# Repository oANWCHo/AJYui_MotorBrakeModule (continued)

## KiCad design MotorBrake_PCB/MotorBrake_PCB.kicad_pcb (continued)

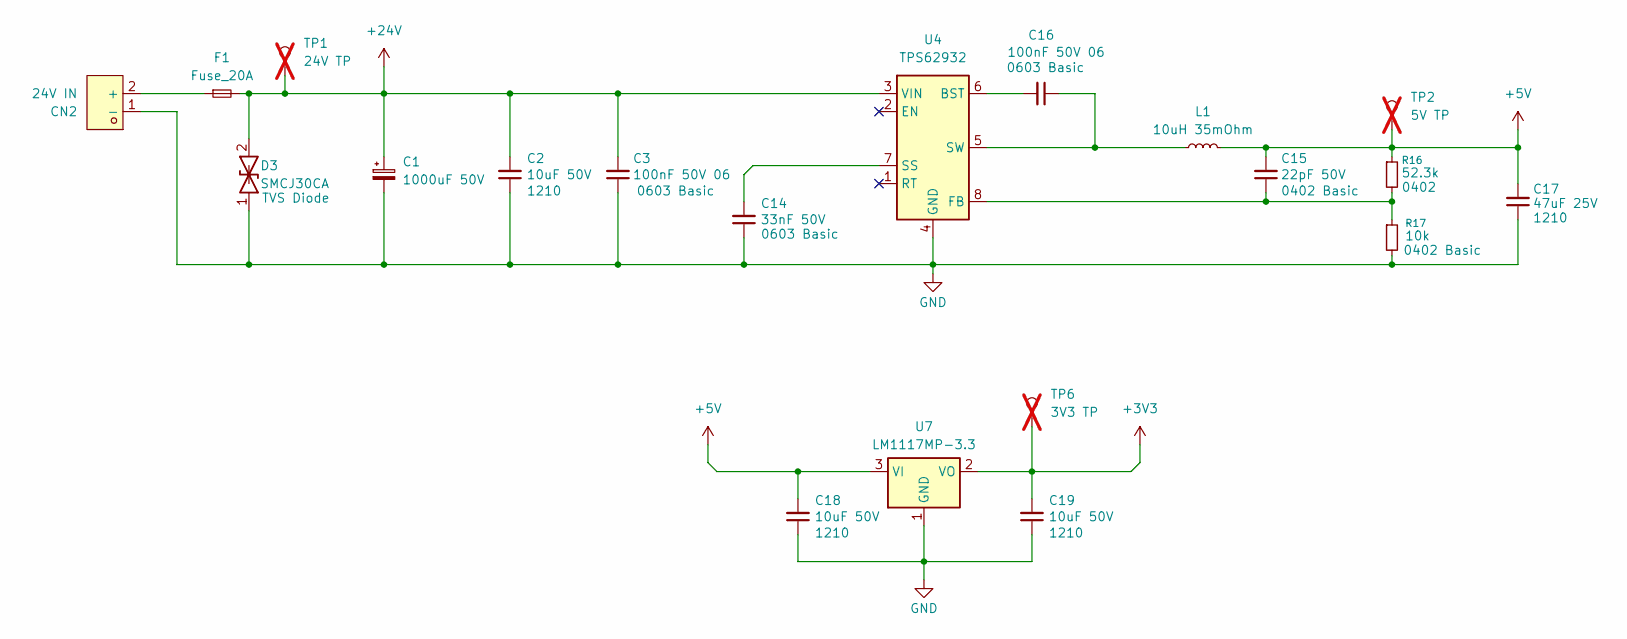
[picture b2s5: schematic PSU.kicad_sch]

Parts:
C1: 1000uF 50V; CP_Elec_16x17.5; JLCPCB Part # C5266058
C2, C18, C19: 10uF 50V; C_1210_3225Metric; JLCPCB Part # C2918502
C3, C16: 100nF 50V 06; C_0603_1608Metric; JLCPCB Part # C14663
C14: 33nF 50V; C_0603_1608Metric; JLCPCB Part # C21117
C15: 22pF 50V; C_0402_1005Metric; JLCPCB Part # C1555
C17: 47uF 25V; C_1210_3225Metric; JLCPCB Part # C6120020
CN2: 24V IN; CONN-TH_XT30UPB-M; Manufacturer Part XT30UPB-M; LCSC Part Name AMASS(艾迈斯)板载立式 航模锂电池控制器连接器插头 PCB板立式 公头X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
D3: SMCJ30CA; SMC_L6.9-W5.9-LS7.9-BI; JLCPCB Part # C7470406
F1: Fuse_20A; CONN-TH_XF-507P; JLCPCB Part # C668119
L1: 10uH 35mOhm; L_TechFuse_SL1040; JLCPCB Part # C22463843
R16: 52.3k; R_0402_1005Metric; JLCPCB Part # C26982
R17: 10k; R_0402_1005Metric; JLCPCB Part # C25744
TP1: 24V TP; TestPoint_Pad_1.0x1.0mm; not fitted
TP2: 5V TP; TestPoint_Pad_1.0x1.0mm; not fitted
TP6: 3V3 TP; TestPoint_Pad_1.0x1.0mm; not fitted
U4: TPS62932; SOT-583-8; JLCPCB Part # C3032935
U7: LM1117MP-3.3; SOT-223-3_TabPin2; JLCPCB Part # C6186

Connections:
+3V3: C19.2, TP6.1 (1_1), U7.2 (VO); also elsewhere on the board
+5V: C15.2, C17.2, C18.2, L1.2, R16.1, TP2.1 (1_1), U7.3 (VI); also elsewhere on the board
+24V: C1.1, C2.2, C3.2, D3.2, F1.2, TP1.1 (1_1), U4.3 (VIN); also elsewhere on the board
GND: C1.2, C2.1, C3.1, C14.1, C17.1, C18.1, C19.1, CN2.1 (-), D3.1, R17.2, U4.4 (GND), U7.1 (GND); also elsewhere on the board
unnamed: CN2.2 (+), F1.1
unnamed: C16.2, U4.6 (BST)
unnamed: C15.1, R16.2, R17.1, U4.8 (FB)
unnamed: C14.2, U4.7 (SS)
unnamed: C16.1, L1.1, U4.5 (SW)

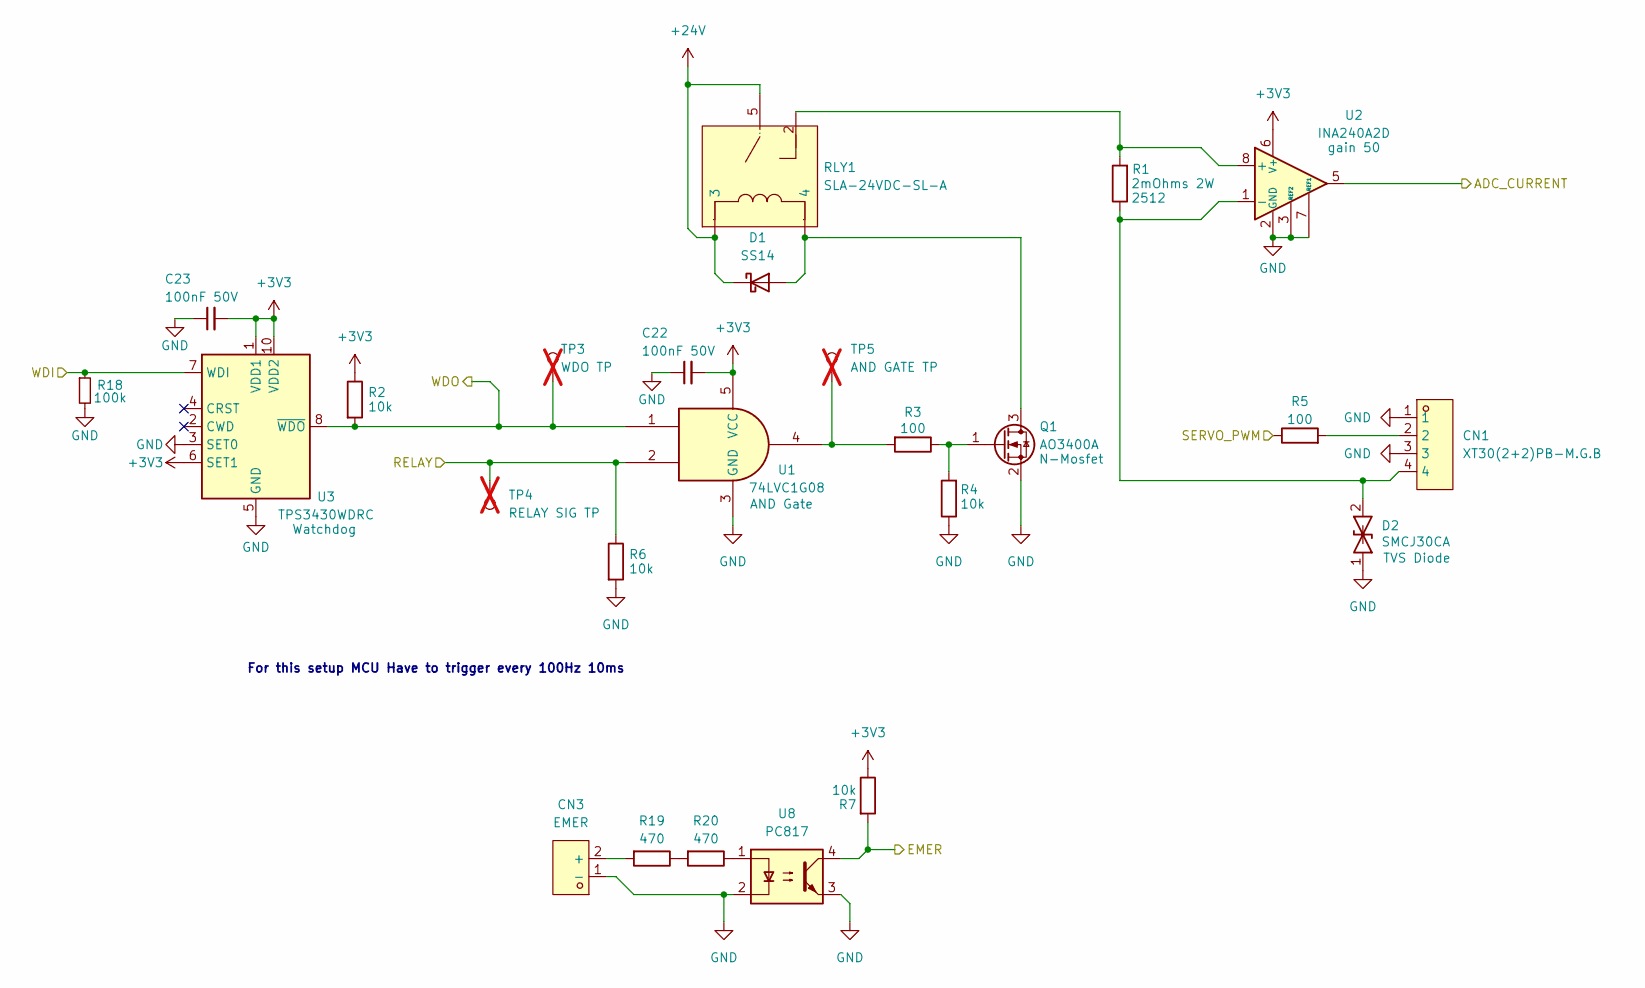
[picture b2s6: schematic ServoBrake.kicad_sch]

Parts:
C22, C23: 100nF 50V; C_0402_1005Metric; LCSC Part # C1525
CN1: XT30(2+2)PB-M.G.B; CONN-TH_XT30PB-M; Manufacturer Part XT30(2+2)PB-M.G.B; LCSC Part Name AMASS(艾迈斯)功率数据混合插头 PCB直插 板立式 金黑 公头XT30(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
CN3: EMER; CONN-TH_XT30UPB-M; Manufacturer Part XT30UPB-M; LCSC Part Name AMASS(艾迈斯)板载立式 航模锂电池控制器连接器插头 PCB板立式 公头X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
D1: SS14; D_SMA; JLCPCB Part # C2480
D2: SMCJ30CA; SMC_L6.9-W5.9-LS7.9-BI; JLCPCB Part # C7470406
Q1: AO3400A; SOT-23; JLCPCB Part # C20917
R1: 2mOhms 2W; R_2512_6332Metric; JLCPCB Part # C844691
R2, R4, R6, R7: 10k; R_0402_1005Metric; JLCPCB Part # C25744
R3, R5: 100; R_0603_1608Metric; JLCPCB Part # C22775
R18: 100k; R_0402_1005Metric; LCSC Part # C25741
R19, R20: 470; R_0603_1608Metric; JLCPCB Part # C23179
RLY1: SLA-24VDC-SL-A; RELAY-TH_SLA-XXVDC-SL-A; Manufacturer Part SLA-24VDC-SL-A; LCSC Part Name 小型大功率继电器(5P)
TP3: WDO TP; TestPoint_Pad_1.0x1.0mm; not fitted
TP4: RELAY SIG TP; TestPoint_Pad_1.0x1.0mm; not fitted
TP5: AND GATE TP; TestPoint_Pad_1.0x1.0mm; not fitted
U1: 74LVC1G08; SOT-23-5; JLCPCB Part # C19829660
U2: INA240A2D; SOIC-8_3.9x4.9mm_P1.27mm; JLCPCB Part # C2060768
U3: TPS3430WDRC; VSON-10-1EP_3x3mm_P0.5mm_EP1.65x2.4mm; JLCPCB Part # C2870545
U8: PC817; DIP-4_W7.62mm; JLCPCB Part # C5350

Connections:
+3V3: C22.2, C23.2, R2.1, R7.1, U1.5 (VCC), U2.6 (V+), U3.1 (VDD1), U3.6 (SET1), U3.10 (VDD2); also elsewhere on the board
+24V: D1.1 (K), RLY1.3, RLY1.5; also elsewhere on the board
/MCU/ADC_CURRENT: U2.5; also elsewhere on the board
/MCU/PC13: R7.2, U8.4; also elsewhere on the board
/MCU/RELAY: R6.1, TP4.1 (1_1), U1.2; also elsewhere on the board
/MCU/SERVO_PWM: R5.1; also elsewhere on the board
/MCU/WDI: R18.1, U3.7 (WDI); also elsewhere on the board
/MCU/WDO: R2.2, TP3.1 (1_1), U1.1, U3.8 (~WDO); also elsewhere on the board
GND: C22.1, C23.1, CN1.1, CN1.3, CN3.1 (-), D2.1, Q1.2 (S), R4.1, R6.2, R18.2, U1.3 (GND), U2.2 (GND), U2.3 (REF2), U2.4 (GND), U2.7 (REF1), U3.3 (SET0), U3.5 (GND), U3.11 (GND), U8.2, U8.3; also elsewhere on the board
unnamed: CN1.2, R5.2
unnamed: CN3.2 (+), R19.2
unnamed: D1.2 (A), Q1.3 (D), RLY1.4
unnamed: Q1.1 (G), R3.1, R4.2
unnamed: R3.2, TP5.1 (1_1), U1.4
unnamed: R19.1, R20.2
unnamed: R20.1, U8.1
unnamed: R1.2, RLY1.2, U2.8 (+)
unnamed: CN1.4, D2.2, R1.1, U2.1 (-)

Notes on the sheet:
For this setup MCU Have to trigger every 100Hz 10ms

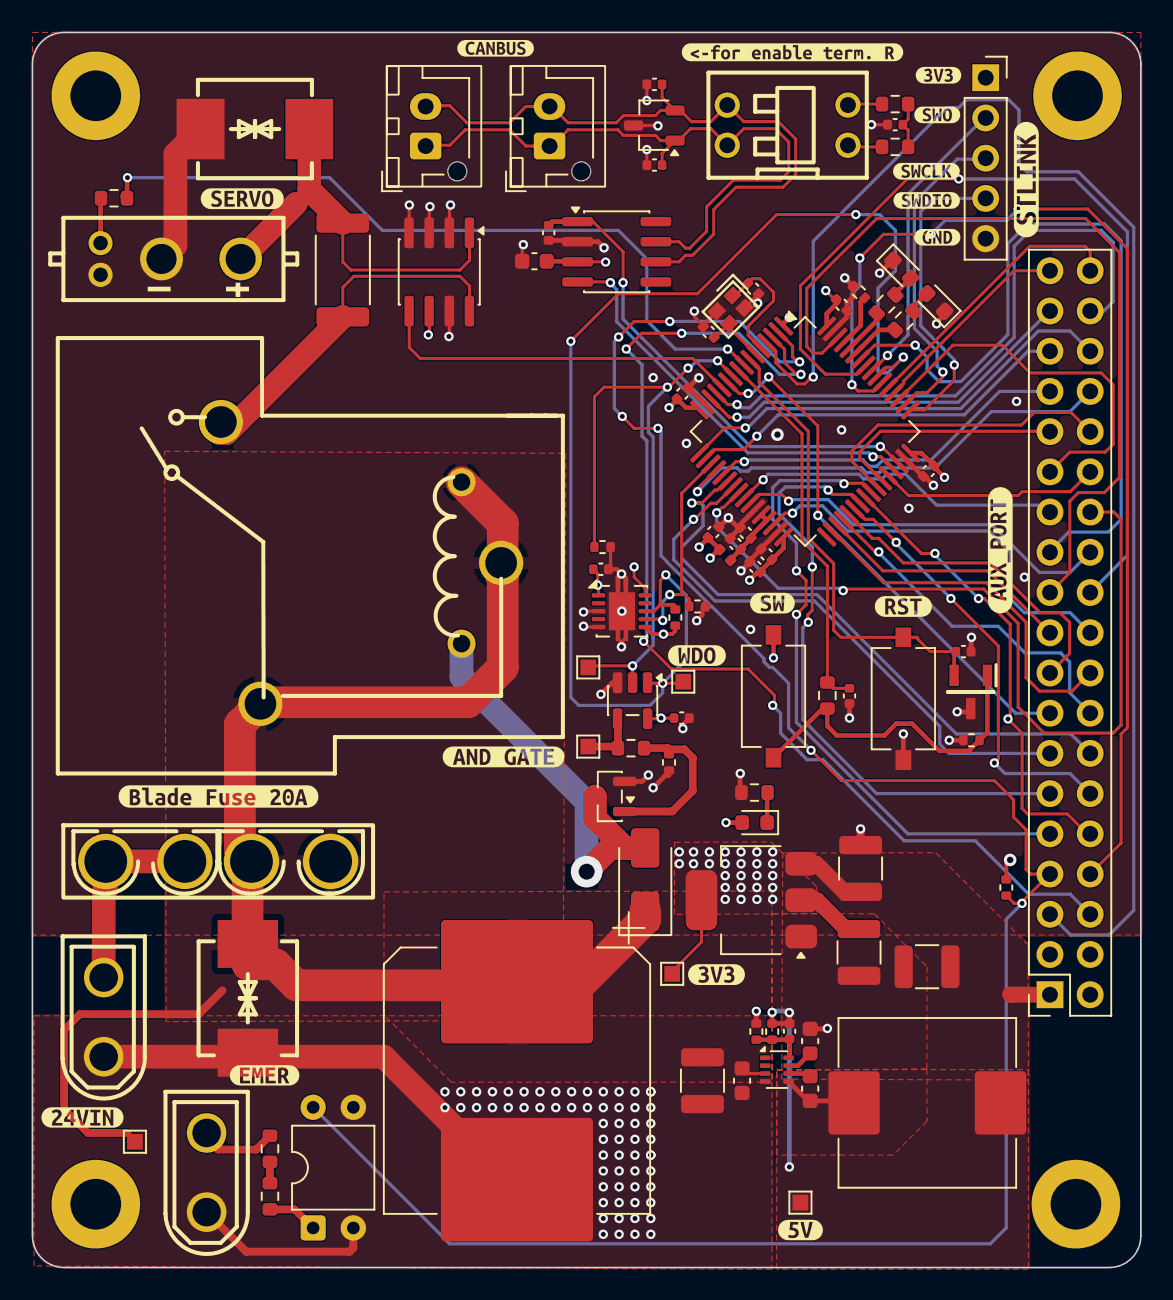
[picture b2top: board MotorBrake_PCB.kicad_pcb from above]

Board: 4 copper layers, 70.0 x 78.0 mm, 109 parts (0 on the bottom side), 79 nets.

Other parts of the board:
kibuzzard-6A106EB0: G***; kibuzzard-6A106EB0
kibuzzard-6A106EEC: G***; kibuzzard-6A106EEC
kibuzzard-6A106F6F: G***; kibuzzard-6A106F6F
kibuzzard-6A106F7F: G***; kibuzzard-6A106F7F
kibuzzard-6A106F8B: G***; kibuzzard-6A106F8B
kibuzzard-6A106F32: G***; kibuzzard-6A106F32
kibuzzard-6A106F49: G***; kibuzzard-6A106F49
kibuzzard-6A106FD0: G***; kibuzzard-6A106FD0
kibuzzard-6A106FEE: G***; kibuzzard-6A106FEE
kibuzzard-6A1070AE: G***; kibuzzard-6A1070AE
kibuzzard-6A1070BB: G***; kibuzzard-6A1070BB
kibuzzard-6A1075DC: G***; kibuzzard-6A1075DC
kibuzzard-6A10700E: G***; kibuzzard-6A10700E
kibuzzard-6A10703E: G***; kibuzzard-6A10703E
kibuzzard-6A10705C: G***; kibuzzard-6A10705C
kibuzzard-6A10708F: G***; kibuzzard-6A10708F
kibuzzard-6A10760E: G***; kibuzzard-6A10760E
kibuzzard-6A107020: G***; kibuzzard-6A107020
kibuzzard-6A107033: G***; kibuzzard-6A107033

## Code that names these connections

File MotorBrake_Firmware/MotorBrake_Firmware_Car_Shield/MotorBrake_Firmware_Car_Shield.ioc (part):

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Mcu.Name=STM32G474R(B-C-E)Tx
Mcu.Package=LQFP64
Mcu.UserName=STM32G474RETx
PA0.Mode=IN1-Single-Ended
PA0.Signal=ADC1_IN1
PA1.GPIOParameters=GPIO_Label
PA1.GPIO_Label=MCOR_Speed_Control_IN
PA1.Mode=IN2-Single-Ended
PA1.Signal=ADC1_IN2
PA10.GPIOParameters=GPIO_Label
PA10.GPIO_Label=Relay_Mode
PA10.Signal=GPIO_Output
PA11.Mode=FDCAN_Activate
PA11.Signal=FDCAN1_RX
PA12.Mode=FDCAN_Activate
PA12.Signal=FDCAN1_TX
PA13.Mode=Serial_Wire
PA13.Signal=SYS_JTMS-SWDIO
PA14.Mode=Serial_Wire
PA14.Signal=SYS_JTCK-SWCLK
PA15.GPIOParameters=GPIO_Label
PA15.GPIO_Label=Speed_Sensor_to_MCU
PA15.Signal=S_TIM2_CH1
PA2.Mode=IN3-Single-Ended
PA2.Signal=ADC1_IN3
PA3.Mode=IN4-Single-Ended
PA3.Signal=ADC1_IN4
PA5.GPIOParameters=GPIO_Label
PA5.GPIO_Label=WDI
PA5.Signal=GPIO_Output
PA8.GPIOParameters=GPIO_Label
PA8.GPIO_Label=MCP4725_SDA
PA8.Mode=I2C
PA8.Signal=I2C2_SDA
PA9.GPIOParameters=GPIO_Label
PA9.GPIO_Label=MCP4725_SCL
PA9.Mode=I2C
PA9.Signal=I2C2_SCL
PB0.GPIOParameters=GPIO_Label
PB0.GPIO_Label=Pedal_IN_to_MCU
PB0.Signal=GPIO_Input
PB5.GPIOParameters=GPIO_Label
PB5.GPIO_Label=LED_1
PB5.Signal=GPIO_Output
PB6.GPIOParameters=GPIO_Label
PB6.GPIO_Label=LED2
PB6.Signal=GPIO_Output
PC0.Signal=S_TIM1_CH1
PC1.GPIOParameters=GPIO_PuPd,GPIO_Label
PC1.GPIO_Label=USER_SW
PC1.GPIO_PuPd=GPIO_PULLDOWN
PC1.Signal=GPIO_Input
PC10.Mode=Asynchronous
PC10.Signal=UART4_TX
PC11.Mode=Asynchronous
PC11.Signal=UART4_RX
PC13.GPIOParameters=GPIO_PuPd,GPIO_Label
PC13.GPIO_Label=E_Stop
PC13.GPIO_PuPd=GPIO_PULLUP
PC13.Signal=GPXTI13
PC2.GPIOParameters=GPIO_Label
PC2.GPIO_Label=RELAY_Brake
PC2.Signal=GPIO_Output
PC4.GPIOParameters=GPIO_Label
PC4.GPIO_Label=Backward_IN_to_MCU
PC4.Signal=GPIO_Input
PC5.GPIOParameters=GPIO_Label
PC5.GPIO_Label=Forward_IN_to_MCU
PC5.Signal=GPIO_Input
PC6.GPIOParameters=GPIO_Label
PC6.GPIO_Label=Forward_IN_from_MCU
PC6.Signal=GPIO_Output
PC7.GPIOParameters=GPIO_Label
PC7.GPIO_Label=Pedal_IN_from_MCU
PC7.Signal=GPIO_Output
PC8.GPIOParameters=GPIO_Label
PC8.GPIO_Label=Backward_IN_from_MCU
PC8.Signal=GPIO_Output
PC9.GPIOParameters=GPIO_Label
PC9.GPIO_Label=MODE_Selector
PC9.Signal=GPIO_Input
PD2.GPIOParameters=GPIO_ModeDefaultEXTI
PD2.GPIO_ModeDefaultEXTI=GPIO_MODE_IT_FALLING
PD2.Signal=GPXTI2
PF0-OSC_IN.Mode=HSE-External-Oscillator
PF0-OSC_IN.Signal=RCC_OSC_IN
PF1-OSC_OUT.Mode=HSE-External-Oscillator
PF1-OSC_OUT.Signal=RCC_OSC_OUT
RCC.HSE_VALUE=32000000
RCC.SYSCLKFreq_VALUE=170000000
RCC.SYSCLKSource=RCC_SYSCLKSOURCE_PLLCLK
board=custom

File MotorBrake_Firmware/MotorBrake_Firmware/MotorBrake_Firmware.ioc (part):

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Mcu.Name=STM32G474R(B-C-E)Tx
Mcu.Package=LQFP64
Mcu.UserName=STM32G474RETx
PA0.Mode=IN1-Single-Ended
PA0.Signal=ADC1_IN1
PA1.Mode=IN2-Single-Ended
PA1.Signal=ADC1_IN2
PA11.Mode=FDCAN_Activate
PA11.Signal=FDCAN1_RX
PA12.Mode=FDCAN_Activate
PA12.Signal=FDCAN1_TX
PA13.Mode=Serial_Wire
PA13.Signal=SYS_JTMS-SWDIO
PA14.Mode=Serial_Wire
PA14.Signal=SYS_JTCK-SWCLK
PA2.Mode=IN3-Single-Ended
PA2.Signal=ADC1_IN3
PA3.Mode=IN4-Single-Ended
PA3.Signal=ADC1_IN4
PA5.GPIOParameters=GPIO_Label
PA5.GPIO_Label=WDI
PA5.Signal=GPIO_Output
PB5.GPIOParameters=GPIO_Label
PB5.GPIO_Label=LED_1
PB5.Signal=GPIO_Output
PB6.GPIOParameters=GPIO_Label
PB6.GPIO_Label=LED2
PB6.Signal=GPIO_Output
PC0.Signal=S_TIM1_CH1
PC1.GPIOParameters=GPIO_PuPd,GPIO_Label
PC1.GPIO_Label=USER_SW
PC1.GPIO_PuPd=GPIO_PULLDOWN
PC1.Signal=GPIO_Input
PC2.GPIOParameters=GPIO_Label
PC2.GPIO_Label=RELAY
PC2.Signal=GPIO_Output
PD2.GPIOParameters=GPIO_ModeDefaultEXTI
PD2.GPIO_ModeDefaultEXTI=GPIO_MODE_IT_FALLING
PD2.Signal=GPXTI2
PF0-OSC_IN.Mode=HSE-External-Oscillator
PF0-OSC_IN.Signal=RCC_OSC_IN
PF1-OSC_OUT.Mode=HSE-External-Oscillator
PF1-OSC_OUT.Signal=RCC_OSC_OUT
RCC.HSE_VALUE=32000000
RCC.SYSCLKFreq_VALUE=170000000
RCC.SYSCLKSource=RCC_SYSCLKSOURCE_PLLCLK
board=custom

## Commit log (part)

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2026-06-20 shield pcb
2026-06-20 Routing PCB Finished
2026-06-20 fix silk screen and fix offset rotation for fabrication
2026-06-22 Update PIC and Flashmem 45 degree at init
2026-06-23 fix update to show current servoangle at init
2026-06-26 update sign for invert start-stop motor pos
2026-06-27 update start stop pos setup
2026-06-27 export schematic file
2026-06-28 Update_start_stop servo pos
